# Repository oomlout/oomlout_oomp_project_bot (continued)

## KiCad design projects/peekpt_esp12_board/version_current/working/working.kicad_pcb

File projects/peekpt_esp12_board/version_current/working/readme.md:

# esp12-board by peekpt  
This is a harvested standardized copy of a project from github.  
The original project can be found at:  
https://github.com/peekpt/esp12-board  
Please consult that link for additional, details, files, and license information.  
Note: It was auto harvested and if the original repo had more than one board file or anything out of the ordinary the files here are likely not representative.

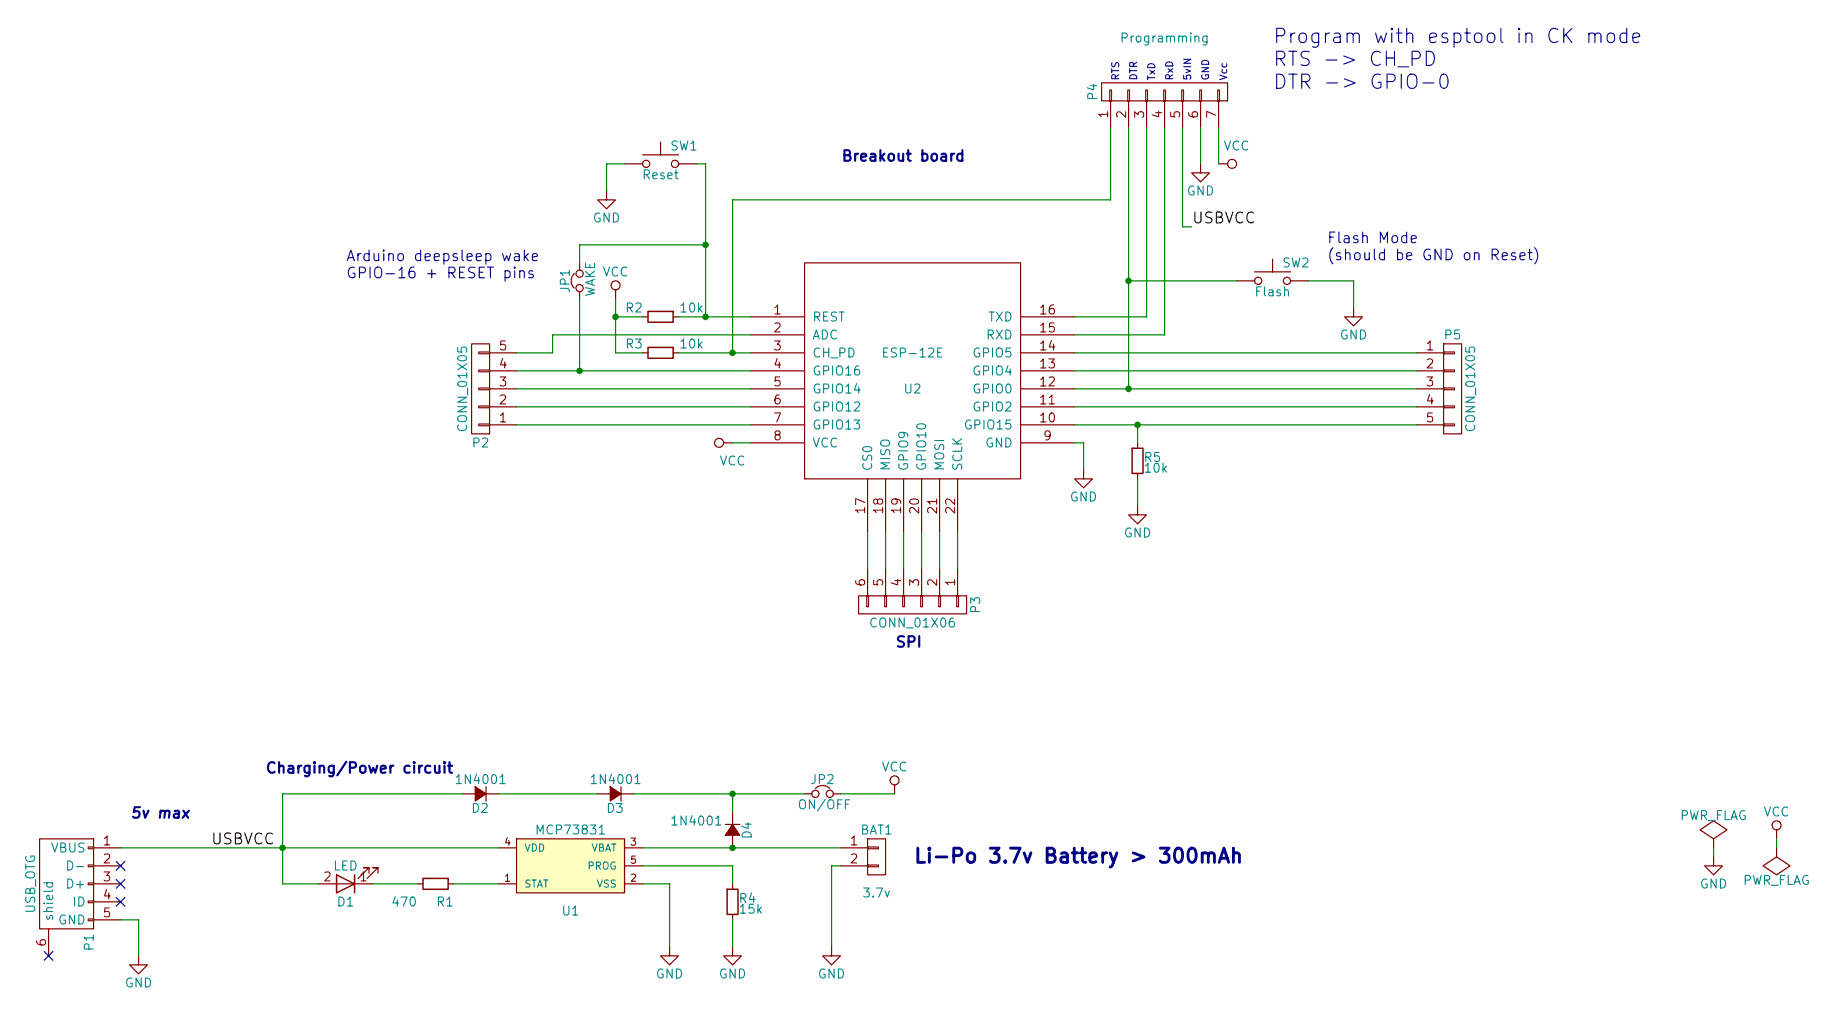
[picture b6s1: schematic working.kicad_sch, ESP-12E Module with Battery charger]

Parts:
BAT1: 3.7v; Pin_Header_Angled_1x02
D1: LED; LED_0805
D2, D3, D4: 1N4001; SMA_Standard
JP1: WAKE; Pin_Header_Straight_1x02
JP2: ON/OFF; Pin_Header_Straight_1x02
P1: USB_OTG; USB_Mini-B
P2, P5: CONN_01X05; Pin_Header_Straight_1x05
P3: CONN_01X06; Pin_Header_Straight_1x06
P4: Programming; Pin_Header_Angled_1x07
R1: 470; R_1206_HandSoldering
R2, R3, R5: 10k; R_1206_HandSoldering
R4: 15k; R_1206_HandSoldering
SW1: Reset; SW_SPST_EVQPE1
SW2: Flash; SW_SPST_EVQPE1
U1: MCP73831; SOT-23-5
U2: ESP-12E

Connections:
/USBVCC: D1.2 (A), D2.2 (A), P1.1 (VBUS), P4.5, U1.4 (VDD)
GND: BAT1.2, P1.5 (GND), P4.6, R4.2, R5.2, SW1.1, SW2.2, U1.2 (VSS), U2.9 (GND)
unnamed: BAT1.1, D4.2 (A), U1.3 (VBAT)
unnamed: D1.1 (K), R1.2
unnamed: D2.1 (K), D3.2 (A)
unnamed: D3.1 (K), D4.1 (K), JP2.1
unnamed: JP1.1, P2.4, U2.4 (GPIO16)
unnamed: JP1.2, R2.1, SW1.2, U2.1 (REST)
unnamed: P2.1, U2.7 (GPIO13)
unnamed: P2.2, U2.6 (GPIO12)
unnamed: P2.3, U2.5 (GPIO14)
unnamed: P2.5, U2.2 (ADC)
unnamed: P3.1, U2.22 (SCLK)
unnamed: P3.2, U2.21 (MOSI)
unnamed: P3.3, U2.20 (GPIO10)
unnamed: P3.4, U2.19 (GPIO9)
unnamed: P3.5, U2.18 (MISO)
unnamed: P3.6, U2.17 (CS0)
unnamed: P4.1, R3.1, U2.3 (CH_PD)
unnamed: P4.2, P5.3, SW2.1, U2.12 (GPIO0)
unnamed: P4.3, U2.16 (TXD)
unnamed: P4.4, U2.15 (RXD)
unnamed: P5.1, U2.14 (GPIO5)
unnamed: P5.2, U2.13 (GPIO4)
unnamed: P5.4, U2.11 (GPIO2)
unnamed: P5.5, R5.1, U2.10 (GPIO15)
unnamed: R1.1, U1.1 (STAT)
unnamed: R4.1, U1.5 (PROG)
VCC: JP2.2, P4.7, R2.2, R3.2, U2.8 (VCC)

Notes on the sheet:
Flash Mode (should be GND on Reset)
Breakout board
5vIN
Vcc
Charging/Power circuit
Li-Po 3.7v Battery > 300mAh
RxD
DTR
SPI
RTS
GND
Arduino deepsleep wake GPIO-16 + RESET pins
5v max
Program with esptool in CK mode RTS -> CH_PD DTR -> GPIO-0
TxD

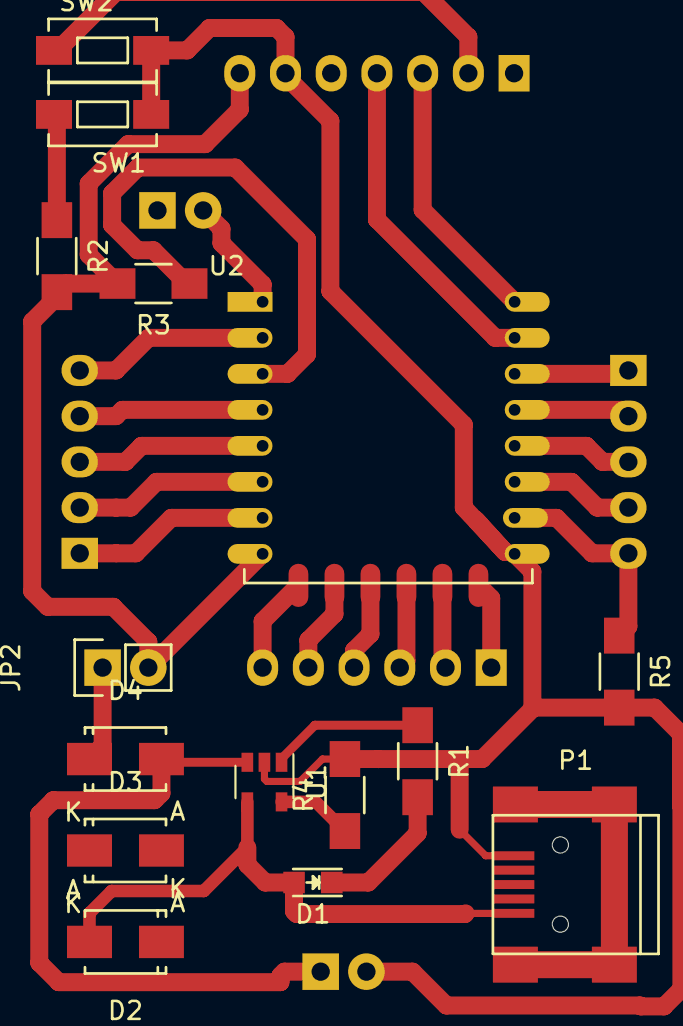
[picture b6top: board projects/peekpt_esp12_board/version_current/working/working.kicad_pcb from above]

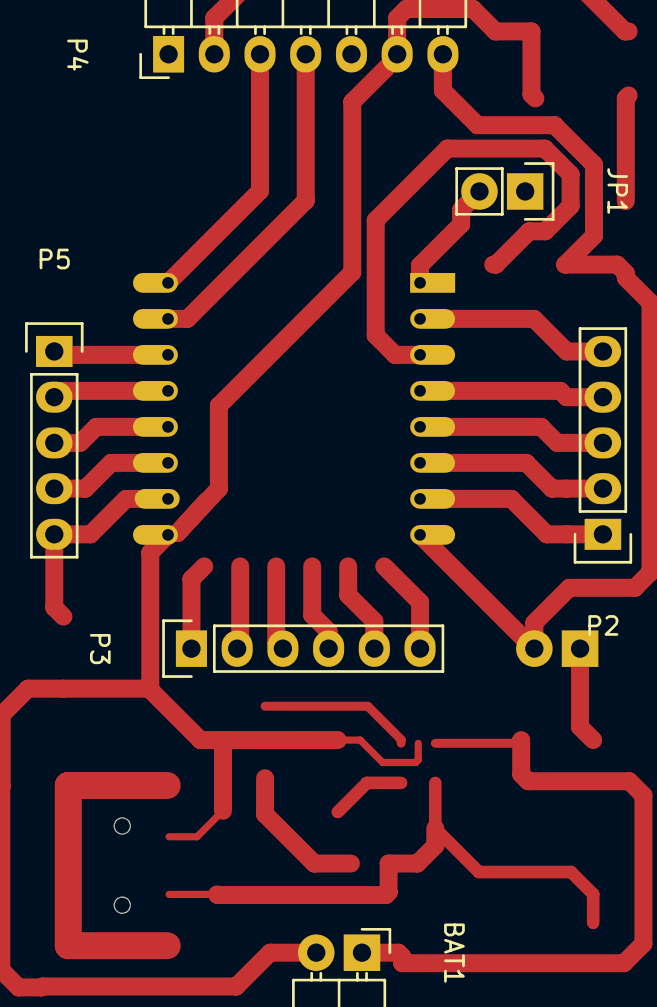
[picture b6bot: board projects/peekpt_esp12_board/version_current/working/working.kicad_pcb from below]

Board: 2 copper layers, 21 parts (6 on the bottom side), 29 nets.

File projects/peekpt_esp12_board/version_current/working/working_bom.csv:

"Id";"Designator";"Footprint";"Quantity";"Designation";"Supplier and ref";
1;"BAT1";"Pin_Header_Angled_1x02";1;"3.7v";;;
2;"D1";"LED_0805";1;"LED";;;
3;"JP1";"Pin_Header_Straight_1x02";1;"WAKE";;;
4;"JP2";"Pin_Header_Straight_1x02";1;"ON/OFF";;;
5;"P1";"USB_Mini-B";1;"USB_OTG";;;
6;"P2,P5";"Pin_Header_Straight_1x05";2;"CONN_01X05";;;
7;"P3";"Pin_Header_Straight_1x06";1;"CONN_01X06";;;
8;"P4";"Pin_Header_Angled_1x07";1;"Programming";;;
9;"R1";"R_1206_HandSoldering";1;"470";;;
10;"R2,R3,R5";"R_1206_HandSoldering";3;"10k";;;
11;"R4";"R_1206_HandSoldering";1;"15k";;;
12;"SW1";"SW_SPST_EVQPE1";1;"Reset";;;
13;"SW2";"SW_SPST_EVQPE1";1;"Flash";;;
14;"U1";"SOT-23-5";1;"MCP73831";;;
15;"U2";"ESP-12E";1;"ESP-12E";;;
16;"D2,D3,D4";"SMA_Standard";3;"1N4001";;;

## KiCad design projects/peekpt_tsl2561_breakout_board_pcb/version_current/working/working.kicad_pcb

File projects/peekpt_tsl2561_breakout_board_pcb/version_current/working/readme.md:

# TSL2561-breakout-board-PCB by peekpt  
This is a harvested standardized copy of a project from github.  
The original project can be found at:  
https://github.com/peekpt/TSL2561-breakout-board-PCB  
Please consult that link for additional, details, files, and license information.  
Note: It was auto harvested and if the original repo had more than one board file or anything out of the ordinary the files here are likely not representative.

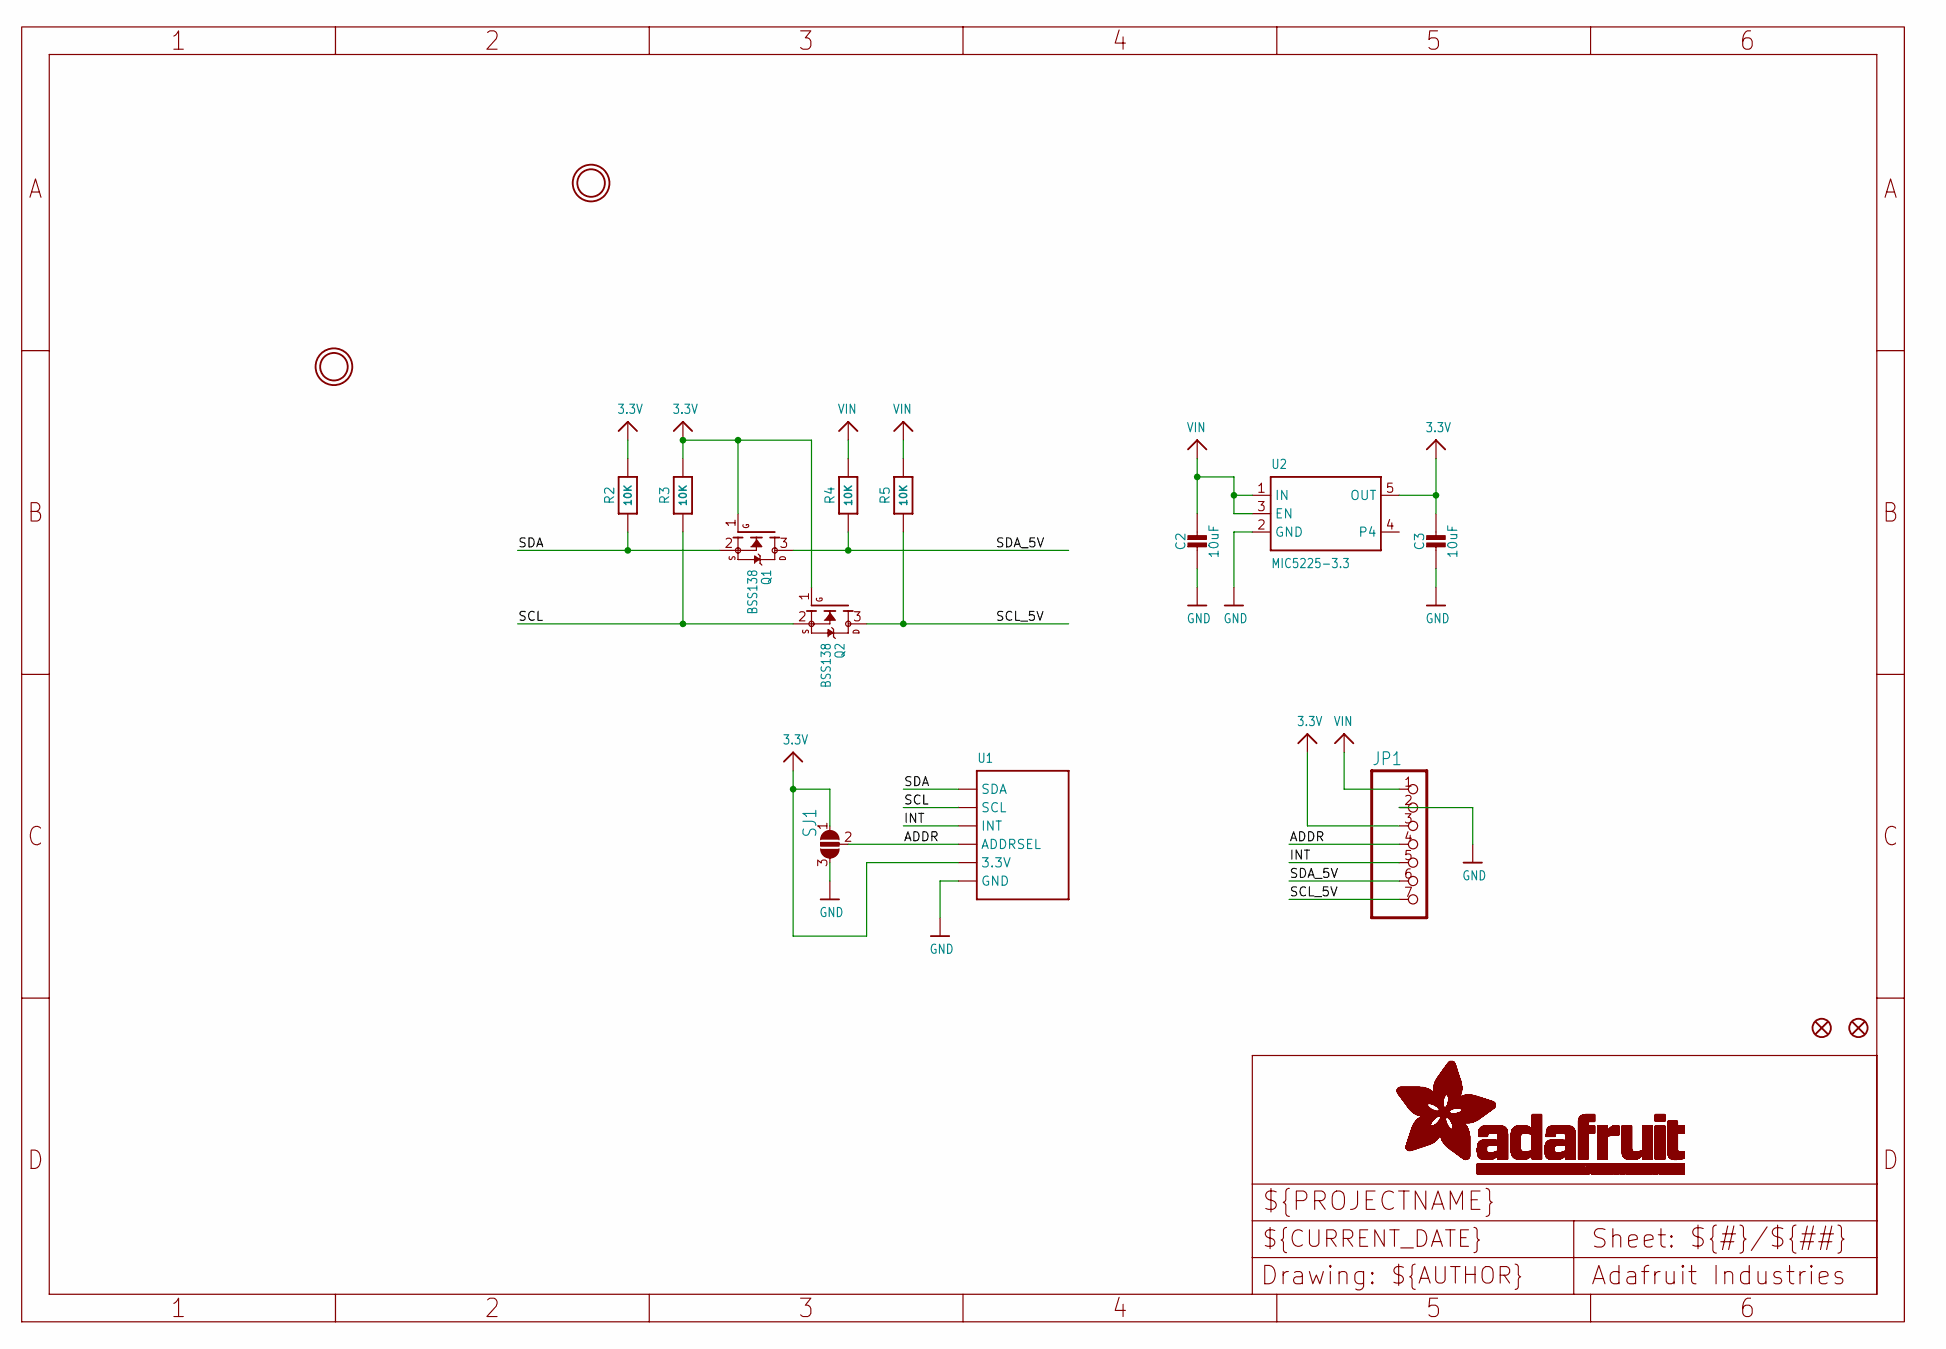
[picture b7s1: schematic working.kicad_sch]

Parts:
C2, C3: 10uF; 0805-NO
FID1, FID2: FIDUCIAL""; FIDUCIAL_1MM
JP1: HEADER-1X7THICKER; 1X07_ROUND_76
Q1, Q2: BSS138; SOT23-WIDE
R2, R3, R4, R5: 10K; 0805-NO
SJ1: SOLDERJUMPER_2WAY; SOLDERJUMPER_2WAY_OPEN_NOPASTE
U1: LIGHT_TSL2561; TSL2561_FN
U2: MIC5225-3.3; SOT23-5
U$18, U$19: MOUNTINGHOLE2.5; MOUNTINGHOLE_2.5_PLATED

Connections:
3.3V: C3.1, JP1.3, Q1.1 (G), Q2.1 (G), R2.2, R3.2, SJ1.1, U1.VDD (3.3V), U2.5 (OUT)
ADDR: JP1.4, SJ1.2, U1.ADR (ADDRSEL)
GND: C2.2, C3.2, JP1.2, SJ1.3, U1.VSS (GND), U2.2 (GND)
INT: JP1.5, U1.INT
SCL: Q2.2 (S), R3.1, U1.CLK (SCL)
SCL_5V: JP1.7, Q2.3 (D), R5.1
SDA: Q1.2 (S), R2.1, U1.DATA (SDA)
SDA_5V: JP1.6, Q1.3 (D), R4.1
VIN: C2.1, JP1.1, R4.2, R5.2, U2.1 (IN), U2.3 (EN)

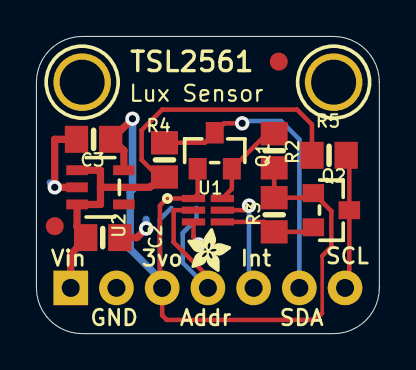
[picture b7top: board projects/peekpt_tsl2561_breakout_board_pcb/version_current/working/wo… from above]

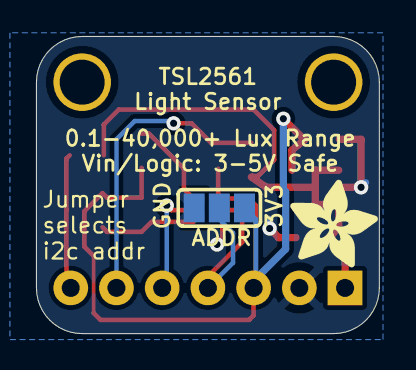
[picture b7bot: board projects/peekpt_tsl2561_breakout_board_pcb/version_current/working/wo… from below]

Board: 2 copper layers, 19.1 x 16.5 mm, 18 parts (2 on the bottom side), 9 nets.

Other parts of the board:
U$15: ADAFRUIT_2.5MM
U$20: ADAFRUIT_5MM

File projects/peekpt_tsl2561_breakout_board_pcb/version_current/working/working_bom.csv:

"Id";"Designator";"Footprint";"Quantity";"Designation";"Supplier and ref";
1;"R2,R4,R3,R5";"0805-NO";4;"10K";;;
2;"Q2,Q1";"SOT23-WIDE";2;"BSS138";;;
3;"FID1,FID2";"FIDUCIAL_1MM";2;"FIDUCIAL""";;;
4;"JP1";"1X07_ROUND_76";1;"";;;
5;"U$19,U$18";"MOUNTINGHOLE_2.5_PLATED";2;"MOUNTINGHOLE2.5";;;
6;"C2,C3";"0805-NO";2;"10uF";;;
7;"U$15";"ADAFRUIT_2.5MM";1;"";;;
8;"U1";"TSL2561_FN";1;"";;;
9;"U2";"SOT23-5";1;"MIC5225-3.3";;;
10;"SJ1";"SOLDERJUMPER_2WAY_OPEN_NOPASTE";1;"";;;
11;"U$20";"ADAFRUIT_5MM";1;"";;;
